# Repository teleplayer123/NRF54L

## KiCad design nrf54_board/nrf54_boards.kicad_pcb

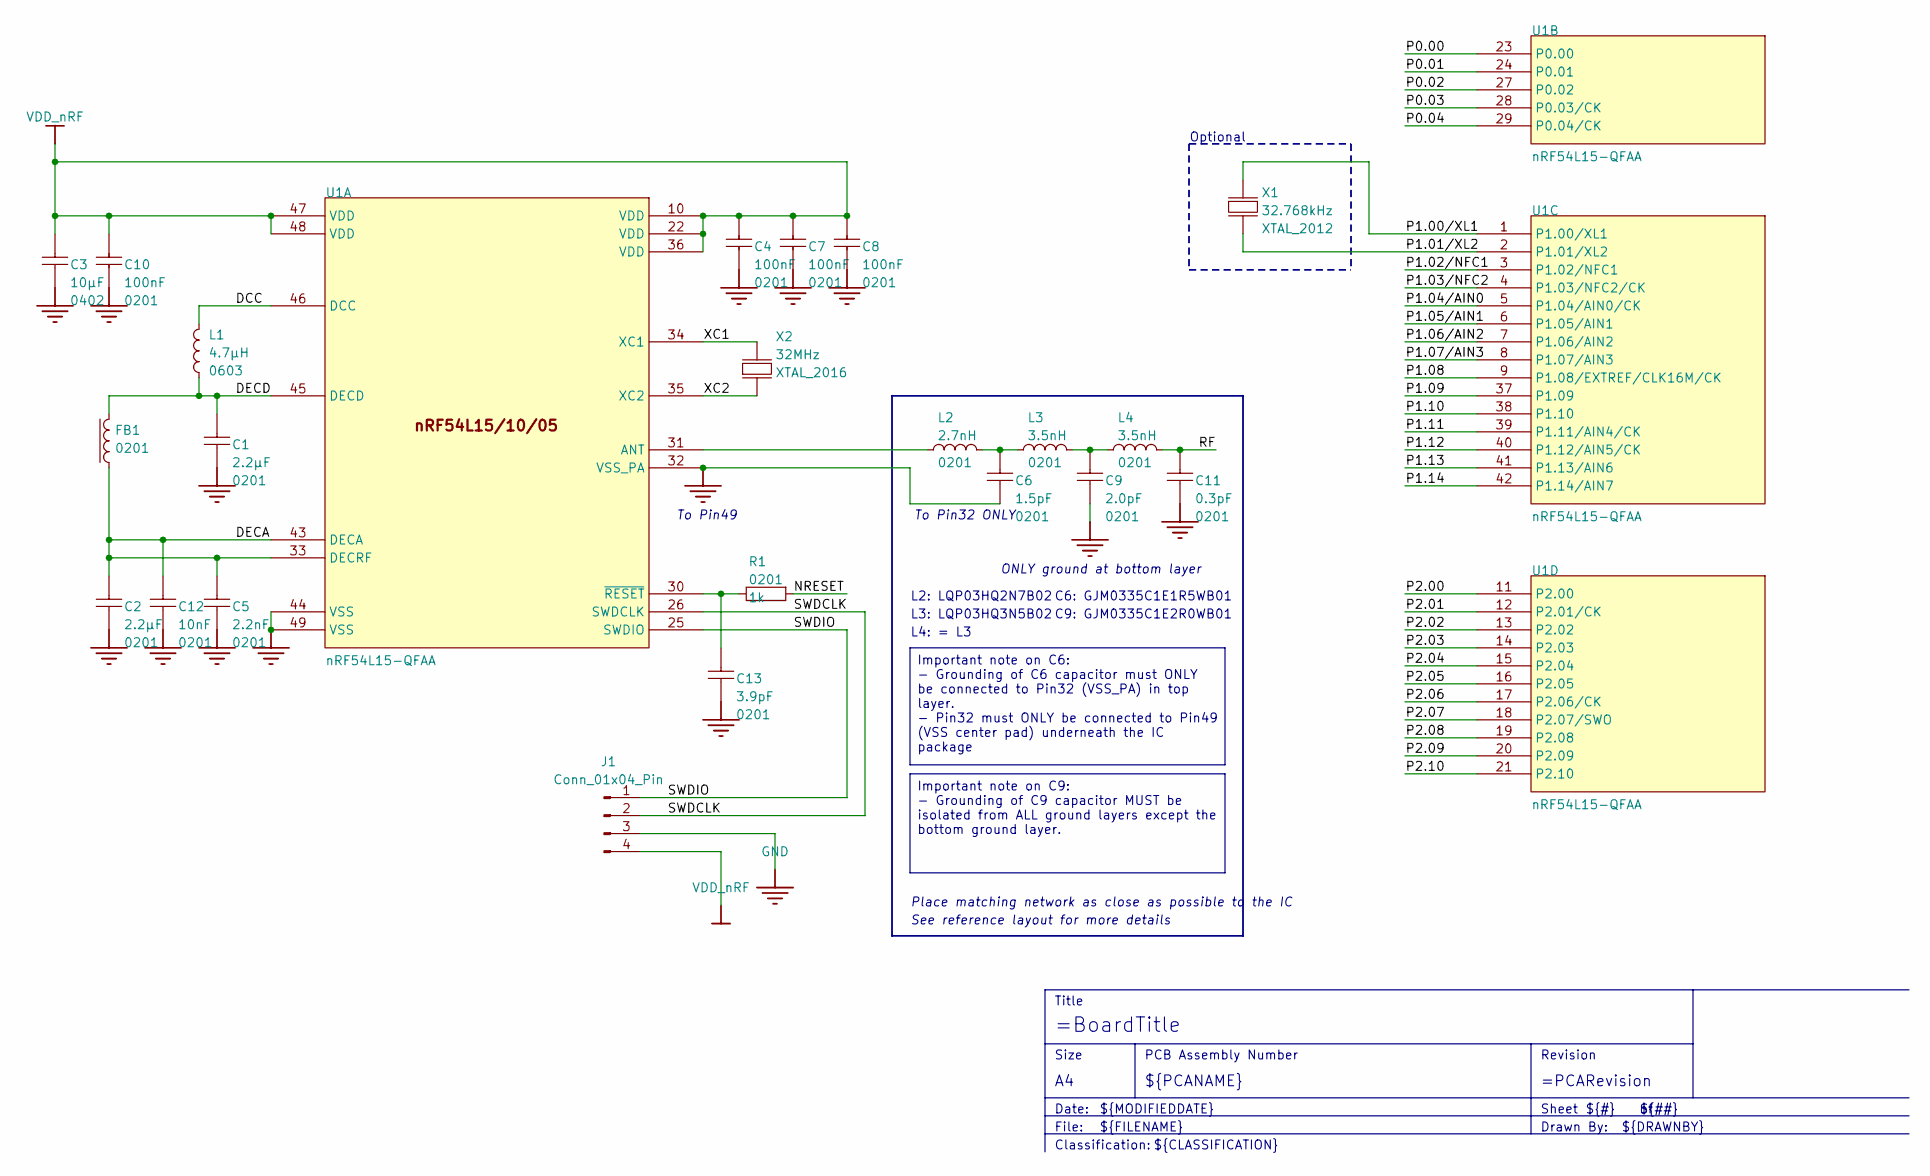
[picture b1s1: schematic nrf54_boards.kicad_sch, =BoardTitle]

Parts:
C1, C2: 2.2µF; C_0201_0603Metric_Pad0.64x0.40mm_HandSolder; PART NUMBER C0201-2µ2-2.5V-X6T-GRM033D80E225ME47D
C3: 10µF; C_0402_1005Metric_Pad0.74x0.62mm_HandSolder; PART NUMBER C0402-10µF-6.3V-X6S
C4, C7, C8, C10: 100nF; C_0201_0603Metric_Pad0.64x0.40mm_HandSolder; PART NUMBER C0201-100n-10V-X7R
C5: 2.2nF; C_0201_0603Metric_Pad0.64x0.40mm_HandSolder; PART NUMBER C0201-2n2
C6: 1.5pF; C_0201_0603Metric_Pad0.64x0.40mm_HandSolder; PART NUMBER C0201-1.5p-25V-NP0-GJM0335C1E1R5WB01
C9: 2.0pF; C_0201_0603Metric_Pad0.64x0.40mm_HandSolder; PART NUMBER C0201-2.0p-HQ-Murata
C11: 0.3pF; C_0201_0603Metric_Pad0.64x0.40mm_HandSolder; PART NUMBER C0201-0.3p-50V-GRM0335C1HR30BA01
C12: 10nF; C_0201_0603Metric_Pad0.64x0.40mm_HandSolder; PART NUMBER C0201-10n-6.3V-X7R
C13: 3.9pF; C_0201_0603Metric_Pad0.64x0.40mm_HandSolder; PART NUMBER C0201-3.9p
FB1: 120R/0.2A; L_0201_0603Metric_Pad0.64x0.40mm_HandSolder; PART NUMBER FB0201-120R@100M-200mA-BLM03AG121SN1D
J1: Conn_01x04_Pin; PinHeader_1x04_P2.54mm_Vertical
L1: 4.7µH; L_0603_1608Metric_Pad1.05x0.95mm_HandSolder; PART NUMBER L0603-4µ7-MLZ1608M4R7WT000
L2: 2.7nH; L_0201_0603Metric_Pad0.64x0.40mm_HandSolder; PART NUMBER L0201-2n7-HQ-Murata
L3, L4: 3.5nH; L_0201_0603Metric_Pad0.64x0.40mm_HandSolder; PART NUMBER L0201-3n5-HQ-Murata
R1: 1k; R_0201_0603Metric_Pad0.64x0.40mm_HandSolder; PART NUMBER R0201-1k0
U1: nRF54L15-QFAA; QFN-48-1EP_6x6mm_P0.4mm_EP4.6x4.6mm; PART NUMBER nRF54L15-QFAA
X1: 32.768kHz; Crystal_SMD_2012-2Pin_2.0x1.2mm_HandSoldering; PART NUMBER XTAL_SMD2012_32.768kHz_9pF_TXC
X2: 32MHz; Crystal_SMD_2016-4Pin_2.0x1.6mm; PART NUMBER XTAL_SMD2016_32MHz_8pF_Kyocera

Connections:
/DCC: L1.1, U1.46 (DCC)
/DECA: C2.2, C5.2, C12.2, FB1.2, U1.33 (DECRF), U1.43 (DECA)
/DECD: C1.2, FB1.1, L1.2, U1.45 (DECD)
/NRESET: R1.2
/P0.00: U1.23 (P0.00)
/P0.01: U1.24 (P0.01)
/P0.02: U1.27 (P0.02)
/P0.03: U1.28 (P0.03/CK)
/P0.04: U1.29 (P0.04/CK)
/P1.00/XL1: U1.1 (P1.00/XL1), X1.2 (out)
/P1.01/XL2: U1.2 (P1.01/XL2), X1.1 (inp)
/P1.02/NFC1: U1.3 (P1.02/NFC1)
/P1.03/NFC2: U1.4 (P1.03/NFC2/CK)
/P1.04/AIN0: U1.5 (P1.04/AIN0/CK)
/P1.05/AIN1: U1.6 (P1.05/AIN1)
/P1.06/AIN2: U1.7 (P1.06/AIN2)
/P1.07/AIN3: U1.8 (P1.07/AIN3)
/P1.08: U1.9 (P1.08/EXTREF/CLK16M/CK)
/P1.09: U1.37 (P1.09)
/P1.10: U1.38 (P1.10)
/P1.11: U1.39 (P1.11/AIN4/CK)
/P1.12: U1.40 (P1.12/AIN5/CK)
/P1.13: U1.41 (P1.13/AIN6)
/P1.14: U1.42 (P1.14/AIN7)
/P2.00: U1.11 (P2.00)
/P2.01: U1.12 (P2.01/CK)
/P2.02: U1.13 (P2.02)
/P2.03: U1.14 (P2.03)
/P2.04: U1.15 (P2.04)
/P2.05: U1.16 (P2.05)
/P2.06: U1.17 (P2.06/CK)
/P2.07: U1.18 (P2.07/SWO)
/P2.08: U1.19 (P2.08)
/P2.09: U1.20 (P2.09)
/P2.10: U1.21 (P2.10)
/RF: C11.2, L4.2
/SWDCLK: J1.2, U1.26 (SWDCLK)
/SWDIO: J1.1, U1.25 (SWDIO)
/XC1: U1.34 (XC1), X2.1 (inp)
/XC2: U1.35 (XC2), X2.3 (out)
GND: C1.1, C2.1, C3.1, C4.2, C5.1, C6.1, C7.2, C8.2, C9.1, C10.2, C11.1, C12.1, C13.1, J1.3, U1.32 (VSS_PA), U1.44 (VSS), U1.49 (VSS)
unnamed: C6.2, L2.2, L3.1
unnamed: C9.2, L3.2, L4.1
unnamed: L2.1, U1.31 (ANT)
unnamed: C13.2, R1.1, U1.30 (~RESET)
VDD_nRF: C3.2, C4.1, C7.1, C8.1, C10.1, J1.4, U1.10 (VDD), U1.22 (VDD), U1.36 (VDD), U1.47 (VDD), U1.48 (VDD)

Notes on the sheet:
${DRAWNBY}
${REVISION}
${CLASSIFICATION}
Revision
To Pin49
Title
Date:
L3: LQP03HQ3N5B02
${TITLE}
${PCANAME}
Place matching network as close as possible to the IC
Size
C6: GJM0335C1E1R5WB01
See reference layout for more details
File:
${MODIFIEDDATE}
Optional
Sheet of
To Pin32 ONLY
C9: GJM0335C1E2R0WB01
L4: = L3
${##}
Classification:
${#}
ONLY ground at bottom layer
Drawn By:
PCB Assembly Number
${FILENAME}
L2: LQP03HQ2N7B02
Important note on C9: - Grounding of C9 capacitor MUST be isolated from ALL ground layers except the bottom ground layer.
Important note on C6: - Grounding of C6 capacitor must ONLY be connected to Pin32 (VSS_PA) in top layer. - Pin32 must ONLY be connected to Pin49 (VSS center pad) underneath the IC package

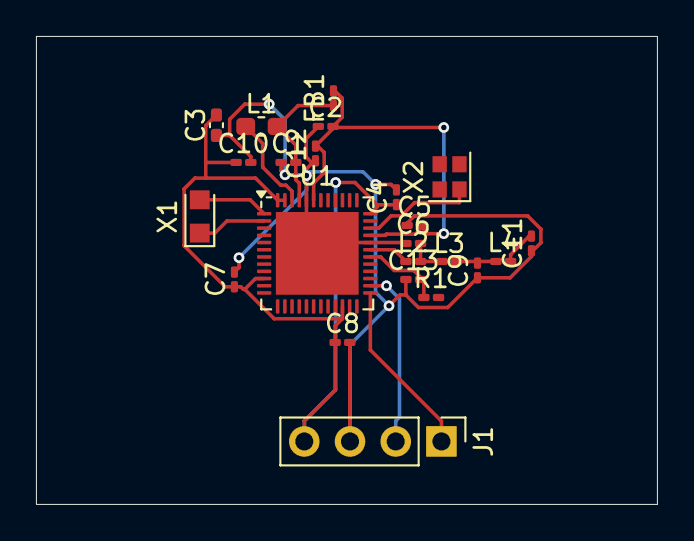
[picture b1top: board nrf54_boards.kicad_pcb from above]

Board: 2 copper layers, 34.5 x 26.0 mm, 23 parts (0 on the bottom side), 16 nets.
